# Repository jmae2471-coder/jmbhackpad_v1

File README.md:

# jmbhackpad_v1
Hey! This is my first time doing anything like this. I want my hackpad to be an aid in video and picture editing, and maybe even a tool to use in the future as I continue to learn how to code. everything needed should be in the files. 
THE SCHEMATIC:

THE PCB:

THE 3D MODEL OF THE CASE

I am using the heat inserts and the screws to put it together. 
BOM:
-4 M3x16mm screws
-4 M3x5mx4mm heatset inserts
-0.91 inch OLED display
-Seeed XIAO RP2040-DIP
-4 blank keycaps
-4 keyboard switches (SW_Push)
-2 RGB LEDS (SK6812 MINI LED)
-2 4.7K resistors 
-3D printed case (top and bottom)

This was a lot of fun to design and create!

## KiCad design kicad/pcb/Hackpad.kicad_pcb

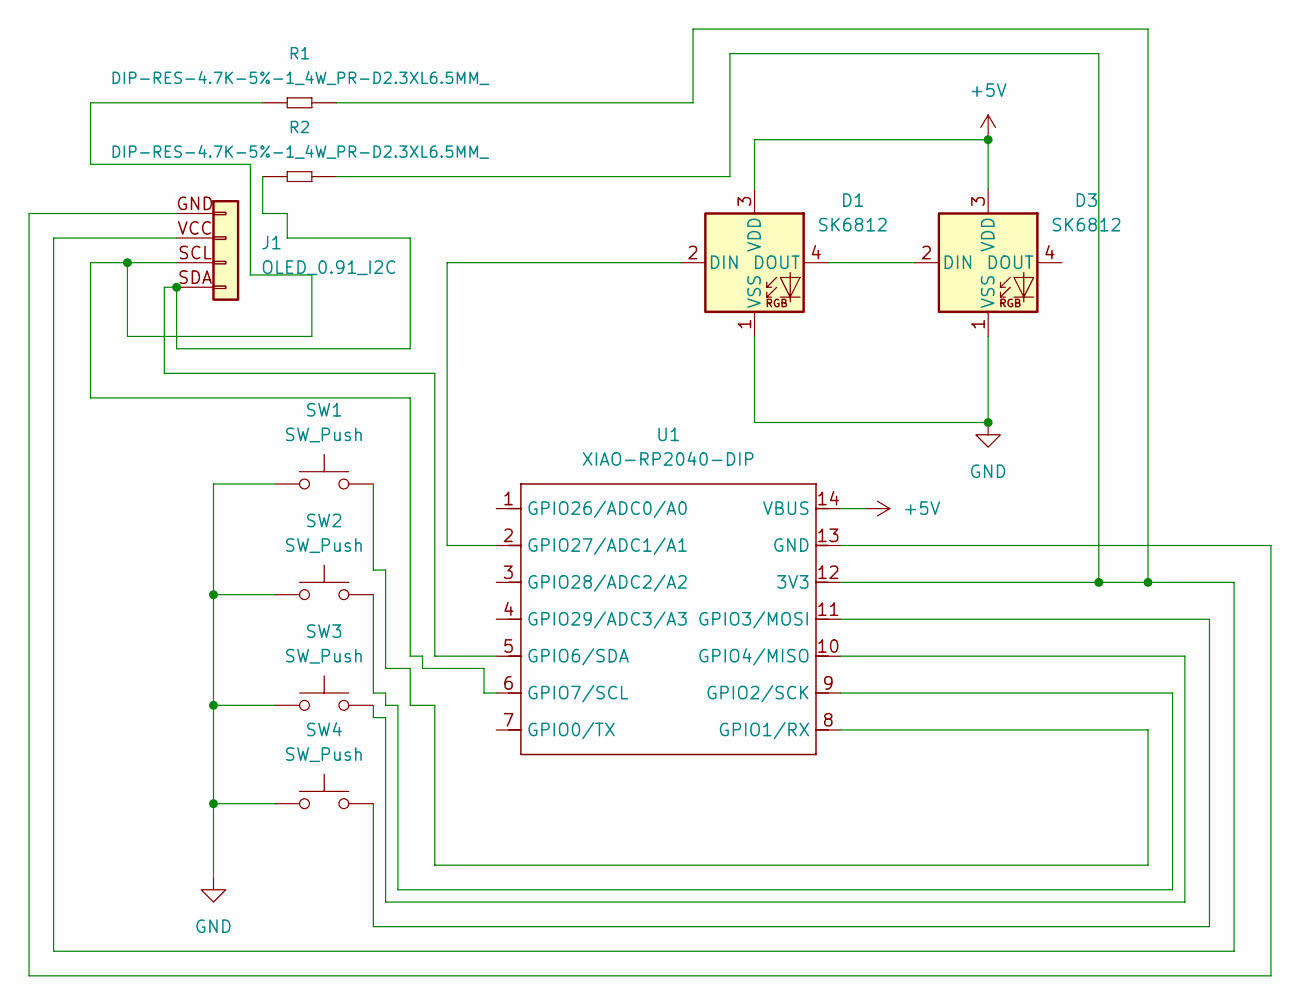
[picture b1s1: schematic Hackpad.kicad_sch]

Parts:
D1, D3: SK6812; LED_SK6812MINI_PLCC4_3.5x3.5mm_P1.75mm
J1: OLED_0.91_I2C
R1, R2: DIP-RES-4.7K-5%-1_4W_PR-D2.3XL6.5MM_; R_0603_1608Metric; MPN FHCFR-1_4W-472J
SW1, SW2, SW3, SW4: SW_Push; SW_Cherry_MX_1.00u_PCB
U1: XIAO-RP2040-DIP

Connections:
+5V: D1.3 (VDD), D3.3 (VDD), U1.14 (VBUS)
GND: D1.1 (VSS), D3.1 (VSS), SW1.1, SW2.1, SW3.1, SW4.1
unnamed: D1.2 (DIN), U1.2 (GPIO27/ADC1/A1)
unnamed: D1.4 (DOUT), D3.2 (DIN)
unnamed: J1.VCC, R1.2, R2.2, U1.12 (3V3)
unnamed: J1.GND, U1.13 (GND)
unnamed: SW1.2, U1.8 (GPIO1/RX)
unnamed: SW2.2, U1.9 (GPIO2/SCK)
unnamed: SW4.2, U1.11 (GPIO3/MOSI)
unnamed: SW3.2, U1.10 (GPIO4/MISO)
unnamed: J1.SDA, R2.1, U1.5 (GPIO6/SDA)
unnamed: J1.SCL, R1.1, U1.6 (GPIO7/SCL)

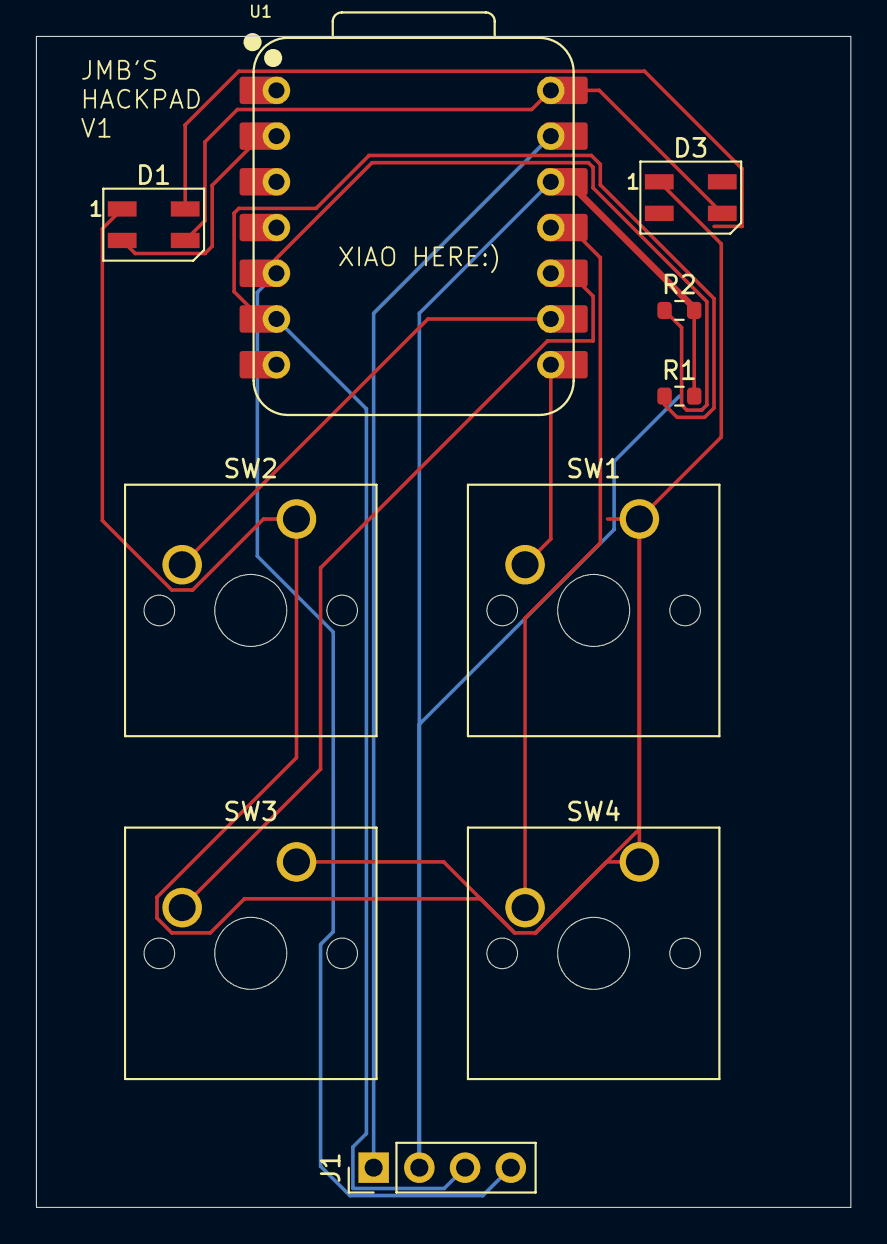
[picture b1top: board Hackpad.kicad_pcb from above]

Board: 2 copper layers, 45.2 x 65.1 mm, 10 parts (0 on the bottom side), 12 nets.

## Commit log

2026-01-19 Create case v1
    top v1 and bottom v2
